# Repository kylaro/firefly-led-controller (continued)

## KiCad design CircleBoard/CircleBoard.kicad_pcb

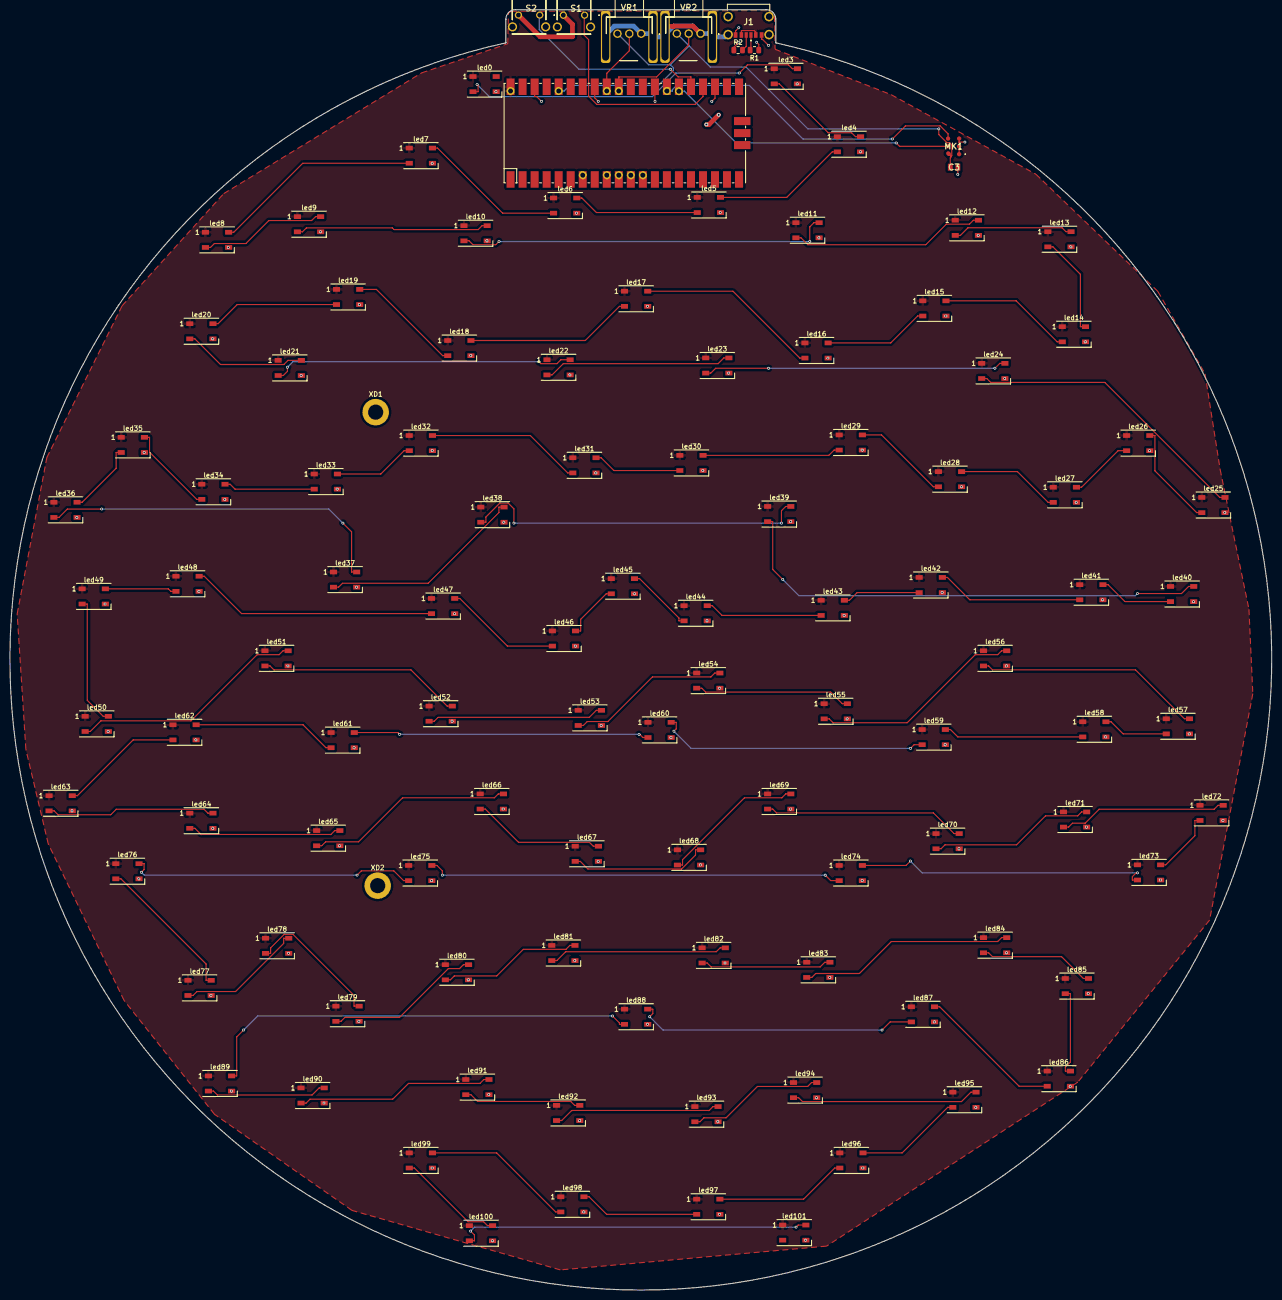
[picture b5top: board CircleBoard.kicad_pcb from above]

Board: 2 copper layers, 266.5 x 270.4 mm, 112 parts (0 on the bottom side), 110 nets.

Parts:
C3: C0805C104M5RAC; CAPC2012X88N
J1: USB4125-GF-A-0190; USB4125GFA0190
MK1: CMM-4737DT-26186-TR; CMM4737DT26186TR
R1, R2: R_US; R_0805_2012Metric
S1, S2: 1-1825027-7; 118250277
U1: Pico; RPi_Pico_SMD_TH_removes2
VR1, VR2: PTV09A-2020F-A104; PTV09A2020FA104
XD1, XD2: MountingHole_3.2mm_M3_DIN965_Pad
led0, led3, led4, led5, led6, led7, led8, led9, led10, led11, led12, led13, led14, led15, led16, led17, led18, led19, led20, led21, led22, led23, led24, led25, led26, led27, led28, led29, led30, led31, led32, led33, led34, led35, led36, led37, led38, led39, led40, led41, led42, led43, led44, led45, led46, led47, led48, led49, led50, led51, led52, led53, led54, led55, led56, led57, led58, led59, led60, led61, led62, led63, led64, led65, led66, led67, led68, led69, led70, led71, led72, led73, led74, led75, led76, led77, led78, led79, led80, led81, led82, led83, led84, led85, led86, led87, led88, led89, led90, led91, led92, led93, led94, led95, led96, led97, led98, led99, led100, led101: LED_WS2812B_PLCC4_5.0x5.0mm_P3.2mm

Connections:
3V3: C3.1, MK1.6 (VDD), U1.36 (3V3), VR1.3 (CW), VR2.3 (CW)
5V: J1.A9 (VBUS_1), J1.B9 (VBUS_2), U1.40 (VBUS), led0.1, led3.1, led4.1, led5.1, led6.1, led7.1, led8.1, led9.1, led10.1, led11.1, led12.1, led13.1, led14.1, led15.1, led16.1, led17.1, led18.1, led19.1, led20.1, led21.1, led22.1, led23.1, led24.1, led25.1, led26.1, led27.1, led28.1, led29.1, led30.1, led31.1, led32.1, led33.1, led34.1, led35.1, led36.1, led37.1, led38.1, led39.1, led40.1, led41.1, led42.1, led43.1, led44.1, led45.1, led46.1, led47.1, led48.1, led49.1, led50.1, led51.1, led52.1, led53.1, led54.1, led55.1, led56.1, led57.1, led58.1, led59.1, led60.1, led61.1, led62.1, led63.1, led64.1, led65.1, led66.1, led67.1, led68.1, led69.1, led70.1, led71.1, led72.1, led73.1, led74.1, led75.1, led76.1, led77.1, led78.1, led79.1, led80.1, led81.1, led82.1, led83.1, led84.1, led85.1, led86.1, led87.1, led88.1, led89.1, led90.1, led91.1, led92.1, led93.1, led94.1, led95.1, led96.1, led97.1, led98.1, led99.1, led100.1, led101.1
BTN_1: S1.1 (COM), U1.24 (GPIO18)
BTN_2: S2.1 (COM), U1.25 (GPIO19)
GND: C3.2, J1.A12 (GND_1), J1.B12 (GND_2), J1.MH1, J1.MH2, J1.MH3, J1.MH4, MK1.1 (GND_1), MK1.2 (L/R), MK1.3 (GND_2), R1.1, R2.1, S1.2 (NO), S2.2 (NO), U1.23 (GND), U1.28 (GND), U1.33 (AGND), U1.38 (GND), VR1.1 (CCW), VR1.MH1, VR1.MH2, VR2.1 (CCW), VR2.MH1, VR2.MH2, led0.3, led3.3, led4.3, led5.3, led6.3, led7.3, led8.3, led9.3, led10.3, led11.3, led12.3, led13.3, led14.3, led15.3, led16.3, led17.3, led18.3, led19.3, led20.3, led21.3, led22.3, led23.3, led24.3, led25.3, led26.3, led27.3, led28.3, led29.3, led30.3, led31.3, led32.3, led33.3, led34.3, led35.3, led36.3, led37.3, led38.3, led39.3, led40.3, led41.3, led42.3, led43.3, led44.3, led45.3, led46.3, led47.3, led48.3, led49.3, led50.3, led51.3, led52.3, led53.3, led54.3, led55.3, led56.3, led57.3, led58.3, led59.3, led60.3, led61.3, led62.3, led63.3, led64.3, led65.3, led66.3, led67.3, led68.3, led69.3, led70.3, led71.3, led72.3, led73.3, led74.3, led75.3, led76.3, led77.3, led78.3, led79.3, led80.3, led81.3, led82.3, led83.3, led84.3, led85.3, led86.3, led87.3, led88.3, led89.3, led90.3, led91.3, led92.3, led93.3, led94.3, led95.3, led96.3, led97.3, led98.3, led99.3, led100.3, led101.3
LINK03: led0.2, led3.4
LINK04: led3.2, led4.4
LINK05: led4.2, led5.4
LINK06: led5.2, led6.4
LINK07: led6.2, led7.4
LINK08: led7.2, led8.4
LINK09: led8.2, led9.4
LINK10: led9.2, led10.4
LINK11: led10.2, led11.4
LINK12: led11.2, led12.4
LINK13: led12.2, led13.4
LINK14: led13.2, led14.4
LINK15: led14.2, led15.4
LINK16: led15.2, led16.4
LINK17: led16.2, led17.4
LINK18: led17.2, led18.4
LINK19: led18.2, led19.4
LINK20: led19.2, led20.4
LINK21: led20.2, led21.4
LINK22: led21.2, led22.4
LINK23: led22.2, led23.4
LINK24: led23.2, led24.4
LINK25: led24.2, led25.4
LINK26: led25.2, led26.4
LINK27: led26.2, led27.4
LINK28: led27.2, led28.4
LINK29: led28.2, led29.4
LINK30: led29.2, led30.4
LINK31: led30.2, led31.4
LINK32: led31.2, led32.4
LINK33: led32.2, led33.4
LINK34: led33.2, led34.4
LINK35: led34.2, led35.4
LINK36: led35.2, led36.4
LINK37: led36.2, led37.4
LINK38: led37.2, led38.4
LINK39: led38.2, led39.4
LINK40: led39.2, led40.4
LINK41: led40.2, led41.4
LINK42: led41.2, led42.4
LINK43: led42.2, led43.4
LINK44: led43.2, led44.4
LINK45: led44.2, led45.4
LINK46: led45.2, led46.4
LINK47: led46.2, led47.4
LINK48: led47.2, led48.4
LINK49: led48.2, led49.4
LINK50: led49.2, led50.4
LINK51: led50.2, led51.4
LINK52: led51.2, led52.4
LINK53: led52.2, led53.4
LINK54: led53.2, led54.4
LINK55: led54.2, led55.4
LINK56: led55.2, led56.4
LINK57: led56.2, led57.4
LINK58: led57.2, led58.4
LINK59: led58.2, led59.4
LINK60: led59.2, led60.4
LINK61: led60.2, led61.4
LINK62: led61.2, led62.4
LINK63: led62.2, led63.4
LINK64: led63.2, led64.4
LINK65: led64.2, led65.4
LINK66: led65.2, led66.4
LINK67: led66.2, led67.4
LINK68: led67.2, led68.4
LINK69: led68.2, led69.4
LINK70: led69.2, led70.4
LINK71: led70.2, led71.4
LINK72: led71.2, led72.4
LINK73: led72.2, led73.4
LINK74: led73.2, led74.4
LINK75: led74.2, led75.4
LINK76: led75.2, led76.4
LINK77: led76.2, led77.4
LINK78: led77.2, led78.4
LINK79: led78.2, led79.4
LINK80: led79.2, led80.4
LINK81: led80.2, led81.4
LINK82: led81.2, led82.4
LINK83: led82.2, led83.4
LINK84: led83.2, led84.4
LINK85: led84.2, led85.4
LINK86: led85.2, led86.4
LINK87: led86.2, led87.4
LINK88: led87.2, led88.4
LINK89: led88.2, led89.4
LINK90: led89.2, led90.4
LINK91: led90.2, led91.4
LINK92: led91.2, led92.4
LINK93: led92.2, led93.4
LINK94: led93.2, led94.4
LINK95: led94.2, led95.4
LINK96: led95.2, led96.4
LINK97: led96.2, led97.4
LINK98: led97.2, led98.4
LINK99: led98.2, led99.4
LINK100: led99.2, led100.4
LINK101: led100.2, led101.4
unnamed: J1.A5 (CC1), R1.2
unnamed: J1.B5 (CC2), R2.2
PDM_CLK: MK1.4 (CLOCK), U1.27 (GPIO21)
PDM_DATA: MK1.5 (DATA), U1.26 (GPIO20)
POT1_ADC: U1.32 (GPIO27_ADC1), VR1.2 (WIPER)
POT2_ADC: U1.31 (GPIO26_ADC0), VR2.2 (WIPER)

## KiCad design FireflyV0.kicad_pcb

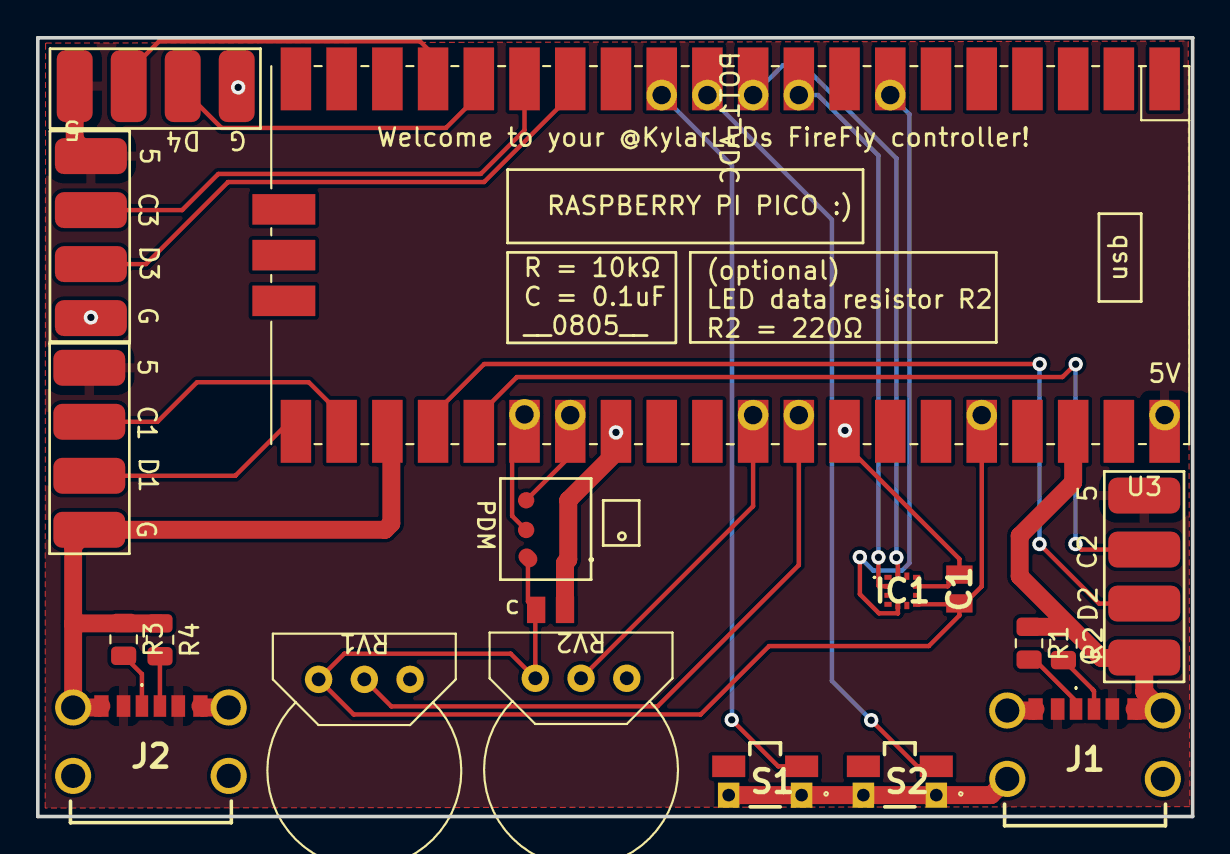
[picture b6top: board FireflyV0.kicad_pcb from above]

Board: 2 copper layers, 64.2 x 43.3 mm, 19 parts (0 on the bottom side), 24 nets.

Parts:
C1, C3: C0805C104M5RAC; CAPC2012X88N
IC1: MXC6655XA
J1, J2: USB4125-GF-A-0190; USB4125GFA0190
MK1: CMM-4737DT-26186-TR; CMM4737DT26186TR
R1, R2, R3, R4: R_US; R_0805_2012Metric
RV1, RV2: R_Potentiometer; 3352T-1-104LF
S1, S2: EVQ-9P701P
U1: Pico; RPi_Pico_SMD_TH_removes2
U2, U3, U4, U5: LEDS4

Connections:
3V3: C1.1, C3.1, IC1.7 (VDD), MK1.6 (VDD), RV1.3, RV2.3, U1.36 (3V3)
5V: J1.A9 (VBUS_1), J1.B9 (VBUS_2), J2.A9 (VBUS_1), J2.B9 (VBUS_2), U1.40 (VBUS), U2.1 (5V), U3.1 (5V), U4.1 (5V), U5.1 (5V)
ACC_CLK: IC1.12 (SCL), U1.10 (GPIO7)
ACC_DATA: IC1.2 (SDA), U1.9 (GPIO6)
ACC_INT: IC1.5 (INT), U1.7 (GPIO5)
BTN_1: S1.2, U1.12 (GPIO9)
BTN_2: S2.2, U1.11 (GPIO8)
GND: C1.2, C3.2, IC1.9 (GND), J1.A12 (GND_1), J1.B12 (GND_2), J1.MH1, J1.MH2, J1.MH3, J1.MH4, J2.A12 (GND_1), J2.B12 (GND_2), J2.MH1, J2.MH2, J2.MH3, J2.MH4, MK1.1 (GND_1), MK1.2 (L/R), MK1.3 (GND_2), R1.1, R2.1, R3.1, R4.1, RV1.1, RV2.1, S1.1, S1.4 (1'), S2.1, S2.4 (1'), U1.23 (GND), U1.28 (GND), U1.33 (AGND), U1.38 (GND), U2.4 (GND), U3.4 (GND), U4.4 (GND), U5.4 (GND)
LED_CLK_1: U1.22 (GPIO17), U2.2 (CLK)
LED_CLK_2: U1.25 (GPIO19), U3.2 (CLK)
LED_CLK_3: U1.15 (GPIO11), U4.2 (CLK)
LED_CLK_4: U1.17 (GPIO13), U5.2 (CLK)
LED_DATA_1: U1.21 (GPIO16), U2.3 (DATA)
LED_DATA_2: U1.24 (GPIO18), U3.3 (DATA)
LED_DATA_3: U1.14 (GPIO10), U4.3 (DATA)
LED_DATA_4: U1.16 (GPIO12), U5.3 (DATA)
unnamed: J1.A5 (CC1), R1.2
unnamed: J1.B5 (CC2), R2.2
unnamed: J2.A5 (CC1), R3.2
unnamed: J2.B5 (CC2), R4.2
PDM_CLK: MK1.4 (CLOCK), U1.27 (GPIO21)
PDM_DATA: MK1.5 (DATA), U1.26 (GPIO20)
POT1_ADC: RV1.2, U1.32 (GPIO27_ADC1)
POT2_ADC: RV2.2, U1.31 (GPIO26_ADC0)

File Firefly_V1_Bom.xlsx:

Part | Quantity | Price | Mouser link | Datasheet link
Pico | 1 | 4 | https://vilros.com/products/raspberry-pi-pico
USBC | 2 | 0.67 | https://www.mouser.com/ProductDetail/GCT/USB4125-GF-A-0190?q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 | https://www.mouser.com/datasheet/2/837/usb4125-2448699.pdf
Mic | 1 | 1.76 | https://www.mouser.com/ProductDetail/CUI-Devices/CMM-4737DT-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 | https://www.mouser.com/datasheet/2/670/cmm_4737dt_26186_tr-1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
Accelerometer | 1 | 1.74 | https://www.mouser.com/ProductDetail/MEMSIC/MXC6655XA?qs=Ged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 | https://www.mouser.com/datasheet/2/821/Memsic_03272020_MXC66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
0.1 uF capacitor | 1 | 0.1 | https://www.mouser.com/ProductDetail/KEMET/C0805C104M5RAC?qs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
3.3 uF capacitor | 1 | 0.31 | https://www.mouser.com/ProductDetail/Kyocera-AVX/0805ZD335MA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
Pot | 2 | 2.5 | https://www.mouser.com/ProductDetail/Bourns/3352T-1-104LF?qs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
Button | 2 | 0.33 | https://www.mouser.com/ProductDetail/Panasonic/EVQ-9P701P?qs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
5.1k resistor | 4

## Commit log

2022-05-30 Initial rev 0
2022-06-26 Adding puttons
2022-06-27 Finished traces and vias, only planes and silkscreen to go
2022-06-27 Done minus accelerometer
2022-06-28 Adding bom, switching switch
2022-06-28 Actual saved pcb this time
2022-06-29 Uploading ordered rev1 files
2022-07-04 Adding circleboard
2022-07-15 CircleBoard updates
2022-07-15 Directory cleanup
2022-08-24 Git rekt
2022-09-10 Front decorated
2022-09-10 All LEDs are connected... not to controller yet
2022-09-10 before clean
2022-09-10 ready for enc and mic
2022-09-10 moved edge cut to center better
2022-09-10 mic and enc almost done
2022-09-10 Mic and Enc ready
2022-09-10 Ordering v2
2022-09-11 Ordered
2024-08-10 Beginning FireFlyV1
2024-08-10 finished first draft of schematic
2024-08-11 lower cost regulator and crystal
2024-08-11 FireFlyV1 power pins
2024-08-11 FireFlyV1 PCB begin
2024-08-11 FireFlyV1 components layout initial thoughts
2024-08-11 Update git ignore
2024-08-12 FireFlyV1 mostly fit on the board
2024-08-12 FireFlyV1 everything on board
2024-08-12 Questionable routing decisions
2024-08-12 Allowed the autorouter to try
2024-08-12 removed unused backup file
2024-08-12 Include LED Footprints
2024-08-13 First JLCPCB Order
2024-08-18 Add BOM and schematic pdfFireFlyV1
2024-08-24 Add FireFlyV1_1 and FireFlyV2 as ordered
2024-09-14 Adding firefly v1.2 and v2.1 as ordered
2024-09-30 Adding FireflyV2.2 as orderable
2024-12-14 FireFlyV3 dev board ordered
2025-08-15 Added V1_3 and V3_1.
2025-08-15 Added V1_2 pdf
